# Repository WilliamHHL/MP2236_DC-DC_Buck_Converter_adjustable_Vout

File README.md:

# PowerModule Base on MP2236

MAX Input Voltage: 18V   
MAX Vout :16V(theoratically)   
Max Iout : 4A(with heatsink 5A)  
Suggested Vin 16V to 12V
Suggested Vout 5V to 3.3V
 
for high Vout and high Iout,heatsink is recommended.
Verified design,but haven't measure the ripple voltage yet.

MP2236 datasheet: https://www.monolithicpower.com/en/documentview/productdocument/index/version/2/document_type/Datasheet/lang/en/sku/MP2236/document_id/4411/

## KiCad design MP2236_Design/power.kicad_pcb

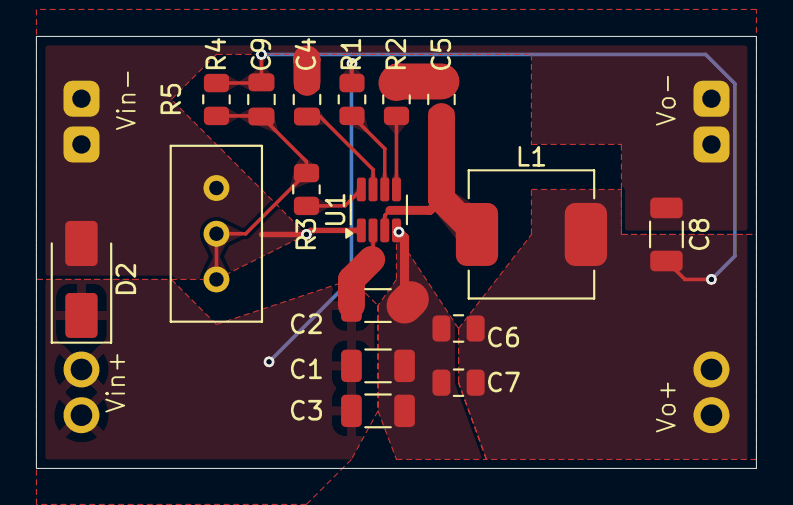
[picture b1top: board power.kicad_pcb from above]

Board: 2 copper layers, 40.0 x 24.0 mm, 21 parts (0 on the bottom side), 10 nets.

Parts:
C1, C2, C8: 22uf; C_1206_3216Metric
C3: 1uf; C_1206_3216Metric
C4, C5: 0.1uf; C_0805_2012Metric
C6, C7: 22uf; C_0805_2012Metric
C9: 220pf; C_0805_2012Metric
D2: SMAJ20A; D_SMA
L1: 4.7uH; L_Changjiang_FXL0630
R1, R4: 200k; R_0805_2012Metric
R2: 10R; R_0805_2012Metric
R3: 0R; R_0805_2012Metric
R5: 100k; Potentiometer_Bourns_3296W_Vertical
U1: TSOT-23-8
U3: V+
Vin-: V-
Vo+: V+
Vo-: V-

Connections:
+12V: C1.2, C2.2, C3.2, D2.1 (A1), R1.1, U1.2 (IN), U3.1 (Vin), U3.2 (Vin)
GND: C1.1, C2.1, C3.1, C4.2, C6.1, C7.1, C8.1, D2.2 (A2), R5.3, U1.1 (AGND), U1.4 (GND), Vin-.1 (GND), Vin-.2 (GND), Vo-.1 (GND), Vo-.2 (GND)
unnamed: C5.2, R2.2
unnamed: C6.2, C7.2, C8.2, C9.1, L1.2, R4.2, Vo+.1 (Vin), Vo+.2 (Vin)
unnamed: C9.2, R3.2, R4.1, R5.1, R5.2
unnamed: R2.1, U1.5 (BST)
unnamed: R1.2, U1.6 (EN)
unnamed: R3.1, U1.8 (FB)
unnamed: C5.1, L1.1, U1.3 (SW)
unnamed: C4.1, U1.7 (VCC)
